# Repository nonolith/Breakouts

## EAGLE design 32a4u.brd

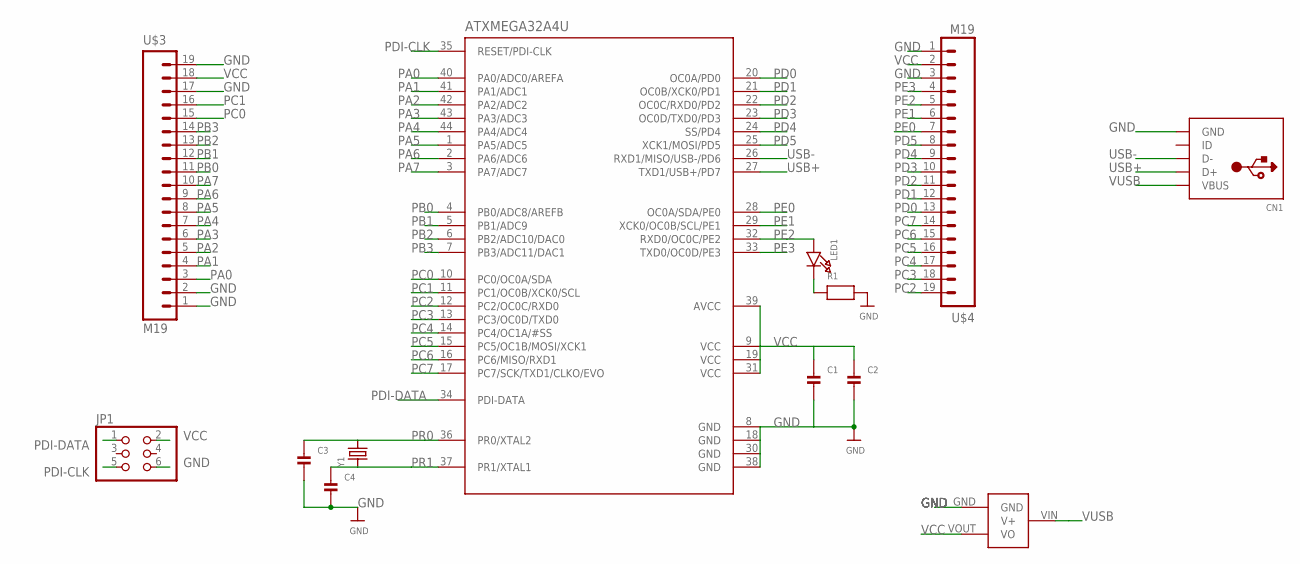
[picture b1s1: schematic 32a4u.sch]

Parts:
ATXMEGA32A4U: ATXMEGAXXA4U-AU; TQFP-44
C1, C2, C3, C4: CAP_CERAMIC0603; 0603
CN1: USBMICROB; USB-MICROB
JP1: HEADER-2X3; 2X03
LED1: LED0603; CHIPLED_0603
R1: RESISTOR0603; 0603
U$2: MCP1700; SOT23-3
U$3, U$4: M19; 1X19
Y1: CRYSTAL; NX8045GB

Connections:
unnamed: LED1.C, R1.1
PA0: ATXMEGA32A4U.40 (PA0/ADC0/AREFA), U$3.3
PA1: ATXMEGA32A4U.41 (PA1/ADC1), U$3.4
PA2: ATXMEGA32A4U.42 (PA2/ADC2), U$3.5
PA3: ATXMEGA32A4U.43 (PA3/ADC3), U$3.6
PA4: ATXMEGA32A4U.44 (PA4/ADC4), U$3.7
PA5: ATXMEGA32A4U.1 (PA5/ADC5), U$3.8
PA6: ATXMEGA32A4U.2 (PA6/ADC6), U$3.9
PA7: ATXMEGA32A4U.3 (PA7/ADC7), U$3.10
PB0: ATXMEGA32A4U.4 (PB0/ADC8/AREFB), U$3.11
PB1: ATXMEGA32A4U.5 (PB1/ADC9), U$3.12
PB2: ATXMEGA32A4U.6 (PB2/ADC10/DAC0), U$3.13
PB3: ATXMEGA32A4U.7 (PB3/ADC11/DAC1), U$3.14
PC0: ATXMEGA32A4U.10 (PC0/OC0A/SDA), U$3.15
PC1: ATXMEGA32A4U.11 (PC1/OC0B/XCK0/SCL), U$3.16
PC2: ATXMEGA32A4U.12 (PC2/OC0C/RXD0), U$4.19
PC3: ATXMEGA32A4U.13 (PC3/OC0D/TXD0), U$4.18
PC4: ATXMEGA32A4U.14 (PC4/OC1A/#SS), U$4.17
PC5: ATXMEGA32A4U.15 (PC5/OC1B/MOSI/XCK1), U$4.16
PC6: ATXMEGA32A4U.16 (PC6/MISO/RXD1), U$4.15
PC7: ATXMEGA32A4U.17 (PC7/SCK/TXD1/CLKO/EVO), U$4.14
PD0: ATXMEGA32A4U.20 (OC0A/PD0), U$4.13
PD1: ATXMEGA32A4U.21 (OC0B/XCK0/PD1), U$4.12
PD2: ATXMEGA32A4U.22 (OC0C/RXD0/PD2), U$4.11
PD3: ATXMEGA32A4U.23 (OC0D/TXD0/PD3), U$4.10
PD4: ATXMEGA32A4U.24 (SS/PD4), U$4.9
PD5: ATXMEGA32A4U.25 (XCK1/MOSI/PD5), U$4.8
PDI-CLK: ATXMEGA32A4U.35 (RESET/PDI-CLK), JP1.5
PDI-DATA: ATXMEGA32A4U.34 (PDI-DATA), JP1.1
PE0: ATXMEGA32A4U.28 (OC0A/SDA/PE0), U$4.7
PE1: ATXMEGA32A4U.29 (XCK0/OC0B/SCL/PE1), U$4.6
PE2: ATXMEGA32A4U.32 (RXD0/OC0C/PE2), LED1.A, U$4.5
PE3: ATXMEGA32A4U.33 (TXD0/OC0D/PE3), U$4.4
PR0: ATXMEGA32A4U.36 (PR0/XTAL2), C3.1, Y1.P$2 (2)
PR1: ATXMEGA32A4U.37 (PR1/XTAL1), C4.1, Y1.P$1 (1)
USB+: ATXMEGA32A4U.27 (TXD1/USB+/PD7), CN1.P3 (D+)
USB-: ATXMEGA32A4U.26 (RXD1/MISO/USB-/PD6), CN1.P2 (D-)
VCC: ATXMEGA32A4U.9 (VCC), ATXMEGA32A4U.19 (VCC), ATXMEGA32A4U.31 (VCC), ATXMEGA32A4U.39 (AVCC), C1.1, C2.1, JP1.2, U$2.VOUT (VO), U$3.18, U$4.2

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
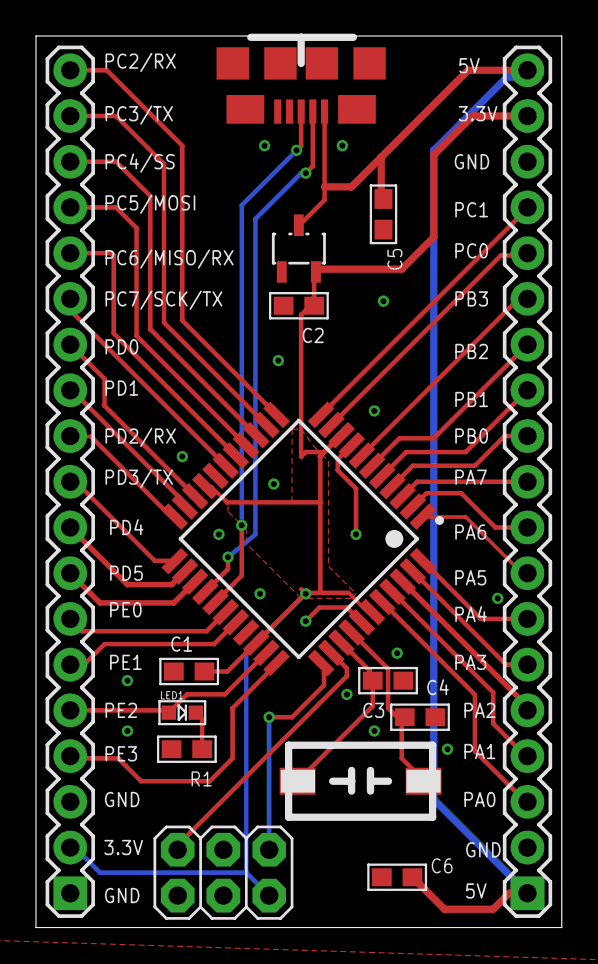
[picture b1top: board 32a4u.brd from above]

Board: 2 copper layers, 29.2 x 49.5 mm, 15 parts (0 on the bottom side), 40 nets.

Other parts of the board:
C5, C6: 0603

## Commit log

2011-07-19 add tqfp44 boards
2011-07-19 add tqfp48 breakout
2011-07-19 reroute crystal ground
2011-08-13 10mil trace width for better clearance
2011-09-20 Add xmega32a4u breakout
2011-09-20 Clean-up schematic, pass Laen DRC
2011-09-21 Add PDI header, remove rev. number from name
2012-11-13 flatten and drop tqfp breakouts
2012-11-13 partially reroute, s/miniusb/microusb/, add crystal
2012-11-13 tweak traces, standardize labeling
2012-11-13 passes fusion DRC
2012-11-13 Clean up: * Route USB as a differential pair * Route crystal more efficiently * Power plane for VCC distribution
2012-11-13 LED on PE2
2012-11-16 routed 5v0 rail to headers, added pair of decoupling capacitors
2012-11-17 10mil isolate on polygons

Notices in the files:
32a4u.brd:
CC-By-SA
